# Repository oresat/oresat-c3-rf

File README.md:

# oresat-c3-rf
RF Sub systems for the C3 board.  This includes the transeiver ICs and all front-end components for the uplink and downlink radios.

## [AxSem_Profiles](AxSem_Profiles)
These are a bunch of profiles that initialize the AxSem RadioLab configuration program for testing and experiments.

## [KiCad](KiCad)
Evaluation board schematics and layouts in KiCad. Some of the older Eagle CAD boards are here converted to KiCAD.

## [block-diagrams](block-diagrams)
Block diagrams of the L band receiver and UHF transceiver hardware.

## [bom](bom)
Inventory and bill-of-materials (BOMs) for evaluation boards.

## [eagle](eagle)
Evaluation board schematics and layouts in EAGLE CAD.

## [link-models](link-models)
Complete link models for command/engineering channels, telemetry/public channels, and bulk mission data channels.

## [measurements](measurements)
Evaluation board measurements using lab tools.

## [simulations](simulations)
Evaluation board simulations using ADS and/or HFSS.

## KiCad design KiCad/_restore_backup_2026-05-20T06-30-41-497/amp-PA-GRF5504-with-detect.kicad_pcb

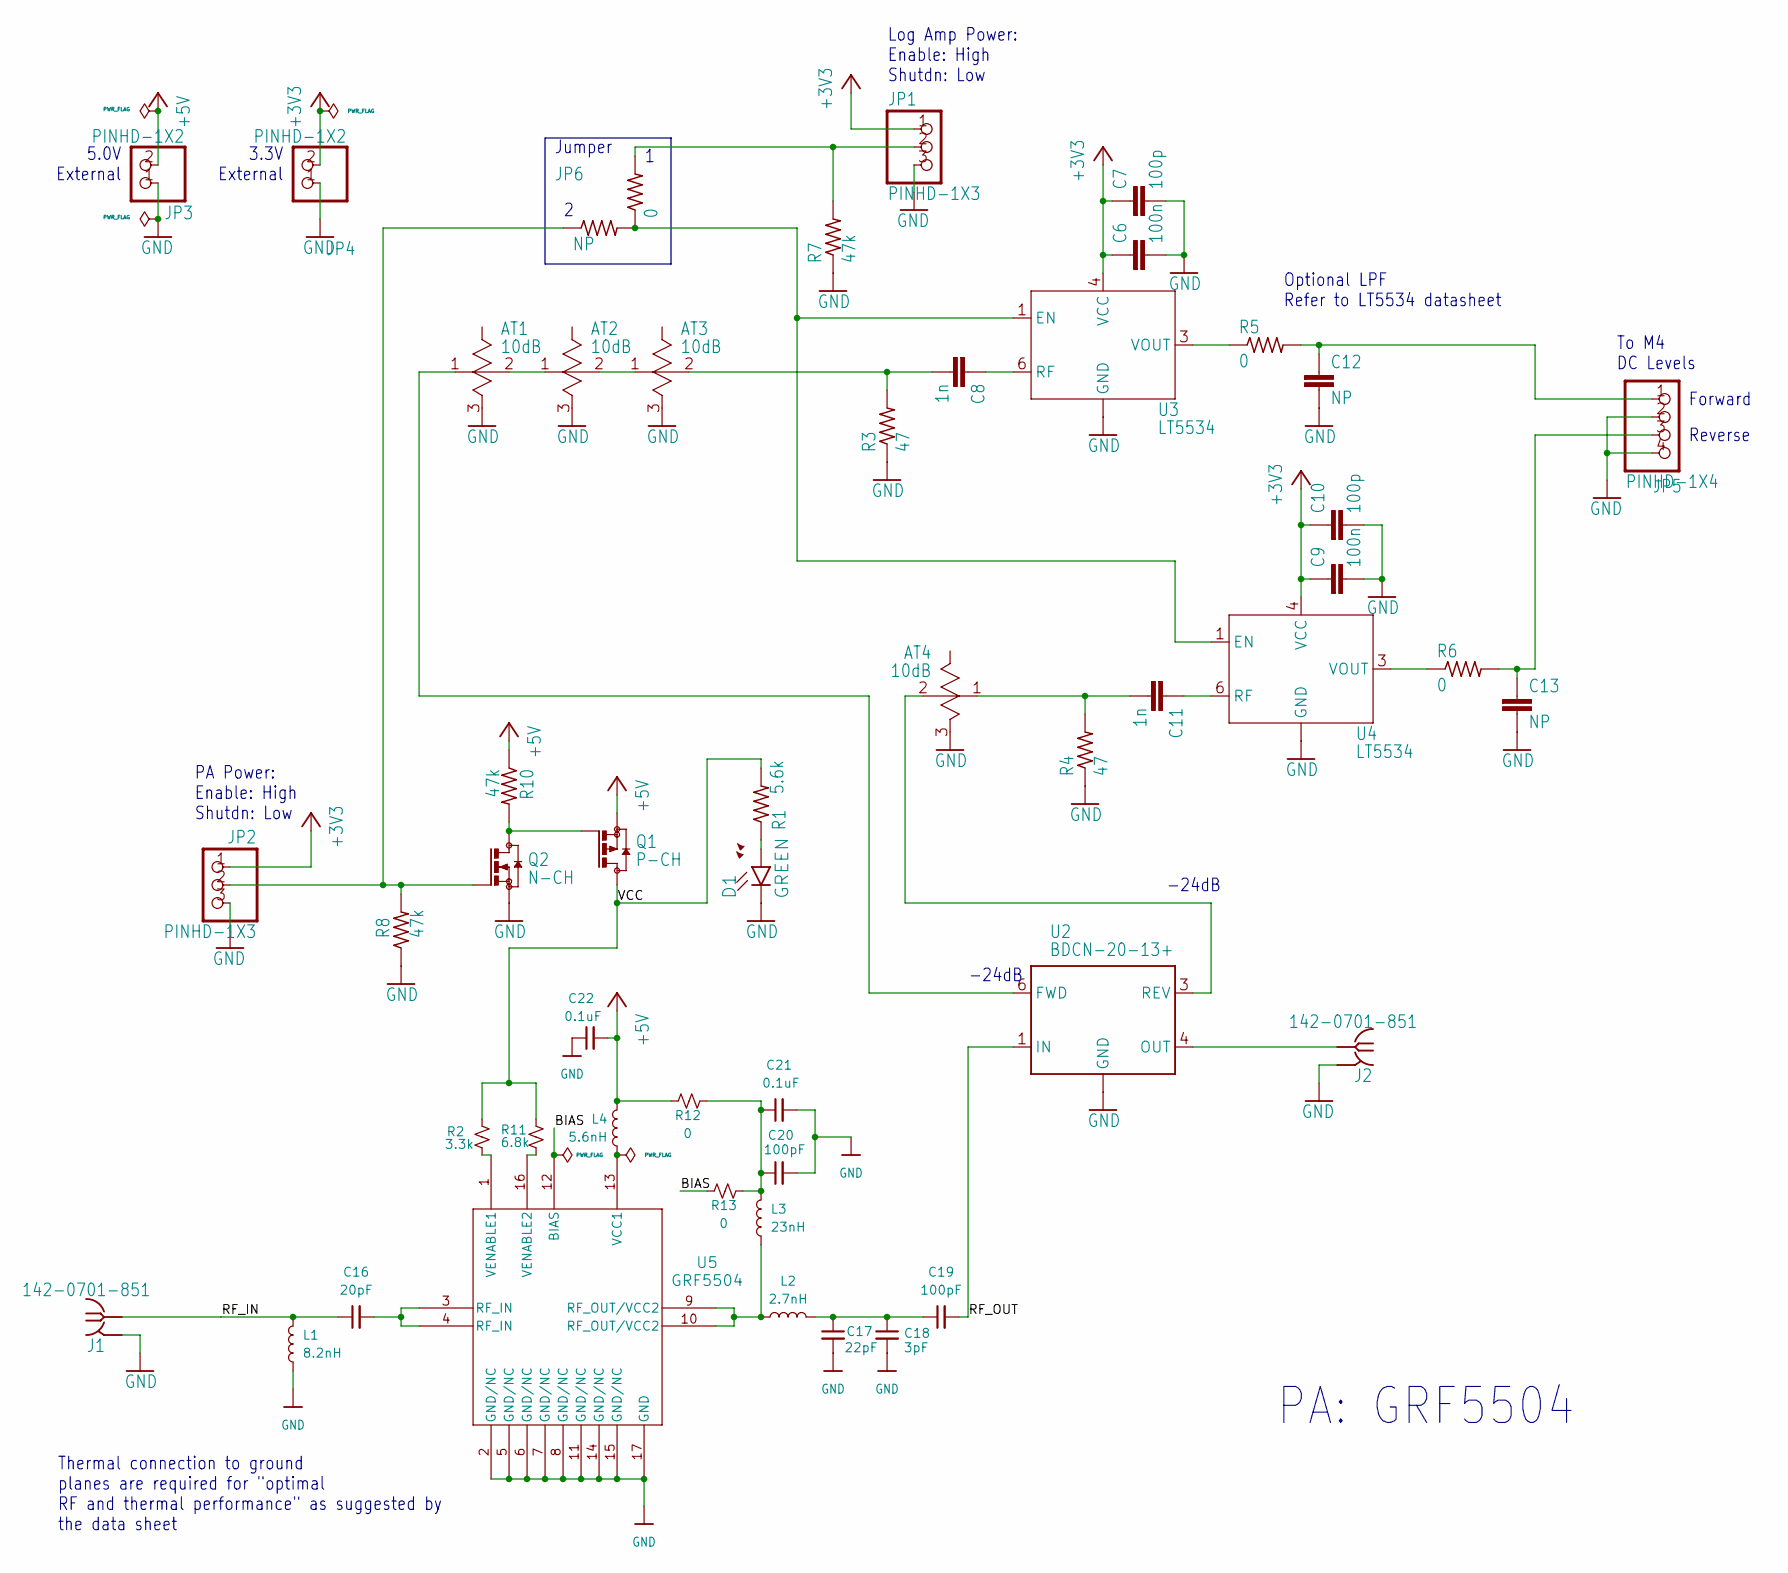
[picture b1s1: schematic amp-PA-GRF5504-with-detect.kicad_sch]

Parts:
AT1: 10dB; 0805
AT2, AT3, AT4: 10dB; 0603
C6, C9: 100n; .0603-B-NOSILK
C7, C10: 100p; .0603-B-NOSILK
C8, C11: 1n; .0402-C-NOSILK
C12, C13: NP; .0603-B-NOSILK
C16: 20pF; .0402-B-NOSILK-GRJ15-GRM15-MURATA-CAPS
C17: 22pF; .0402-B-NOSILK-GRJ15-GRM15-MURATA-CAPS
C18: 3pF; .0402-B-NOSILK-GRJ15-GRM15-MURATA-CAPS
C19, C20: 100pF; .0402-B-NOSILK-GRJ15-GRM15-MURATA-CAPS
C21, C22: 0.1uF; .0402-B-NOSILK-GRJ15-GRM15-MURATA-CAPS
D1: GREEN; LED-0603
J1, J2: 142-0701-851
JP1, JP2: PINHD-1X3; 1X03_325
JP3, JP4: PINHD-1X2; 1X02_325
JP5: PINHD-1X4; 1X04_325
JP6: NP; .0603-B-NOSILK
L1: 8.2nH; .0402-B-NOSILK-LQG-MURATA-INDUCTOR
L2: 2.7nH; .0603-B-NOSILK-DC-COILCRAFT-INDUCTOR
L3: 23nH; 0908-0908SQ-COILCRAFT-INDUCTOR
L4: 5.6nH; .0402-B-NOSILK-HP-DIGITALELECTRONICS-INDUCTOR
Q1: P-CH; SOT23-6
Q2: N-CH; SOT23-6
R1: 5.6k; .0603-B-NOSILK
R2: 3.3k; .0402-B-NOSILK
R3, R4: 47; .0402-C-NOSILK
R5, R6, R9, R12, R13: 0; .0603-B-NOSILK
R7, R8, R10: 47k; .0402-B-NOSILK
R11: 6.8k; .0402-B-NOSILK
U2: BDCN-20-13+
U3, U4: LT5534; SC70
U5: GRF5504; QFN-16_3MM_GRF

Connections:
+3V3: C6.1, C7.1, C9.1, C10.1, JP1.1, JP2.1, JP4.2, U3.4 (VCC), U4.4 (VCC)
+5V: C22.2, JP3.2, L4.1, Q1.2 (S), R10.1, R12.1
/BIAS: R13.1, U5.12 (BIAS)
/RF_IN: C16.1, J1.RF1 (RF), L1.1
/RF_OUT: C19.2, U2.1 (IN)
/VCC: Q1.3 (D), R1.2, R2.1, R11.1
GND: AT1.3 (GND), AT2.3 (GND), AT3.3 (GND), AT4.3 (GND), C6.2, C7.2, C9.2, C10.2, C12.2, C13.2, C17.2, C18.2, C20.2, C21.2, C22.1, D1.C, J1.GND1 (GND), J1.GND2 (GND), J1.GND3 (GND), J1.GND4 (GND), J2.GND1 (GND), J2.GND2 (GND), J2.GND3 (GND), J2.GND4 (GND), JP1.3, JP2.3, JP3.1, JP4.1, JP5.2, JP5.4, L1.2, Q2.2 (S), R3.1, R4.1, R7.1, R8.1, U2.2 (GND), U2.5 (GND), U3.2 (GND), U3.5 (GND), U4.2 (GND), U4.5 (GND), U5.2 (GND/NC), U5.5 (GND/NC), U5.6 (GND/NC), U5.7 (GND/NC), U5.8 (GND/NC), U5.11 (GND/NC), U5.14 (GND/NC), U5.15 (GND/NC), U5.17 (GND)
unnamed: AT1.2, AT2.1
unnamed: AT2.2, AT3.1
unnamed: AT3.2, C8.2, R3.2
unnamed: AT4.1, C11.2, R4.2
unnamed: C12.1, JP5.1, R5.2
unnamed: C13.1, JP5.3, R6.2
unnamed: C16.2, U5.3 (RF_IN), U5.4 (RF_IN)
unnamed: C17.1, C18.1, C19.1, L2.2
unnamed: C20.1, C21.1, L3.2, R12.2, R13.2
unnamed: D1.A, R1.1
unnamed: J2.RF1 (RF), U2.4 (OUT)
unnamed: JP1.2, R7.2, R9.2
unnamed: L2.1, L3.1, U5.9 (RF_OUT/VCC2), U5.10 (RF_OUT/VCC2)
unnamed: Q1.1 (G), Q2.3 (D), R10.2
unnamed: JP2.2, JP6.1, Q2.1 (G), R8.2
unnamed: AT1.1, U2.6 (FWD)
unnamed: AT4.2, U2.3 (REV)
unnamed: JP6.2, R9.1, U3.1 (EN), U4.1 (EN)
unnamed: C8.1, U3.6 (RF)
unnamed: R5.1, U3.3 (VOUT)
unnamed: C11.1, U4.6 (RF)
unnamed: R6.1, U4.3 (VOUT)
unnamed: L4.2, U5.13 (VCC1)
unnamed: R2.2, U5.1 (VENABLE1)
unnamed: R11.2, U5.16 (VENABLE2)

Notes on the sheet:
PA Power: Enable: High Shutdn: Low
Log Amp Power: Enable: High Shutdn: Low
3.3V External
To M4 DC Levels
-24dB
Jumper
PA: GRF5504
Optional LPF Refer to LT5534 datasheet
Thermal connection to ground planes are required for "optimal RF and thermal performance" as suggested by the data sheet
Forward
5.0V External
Reverse

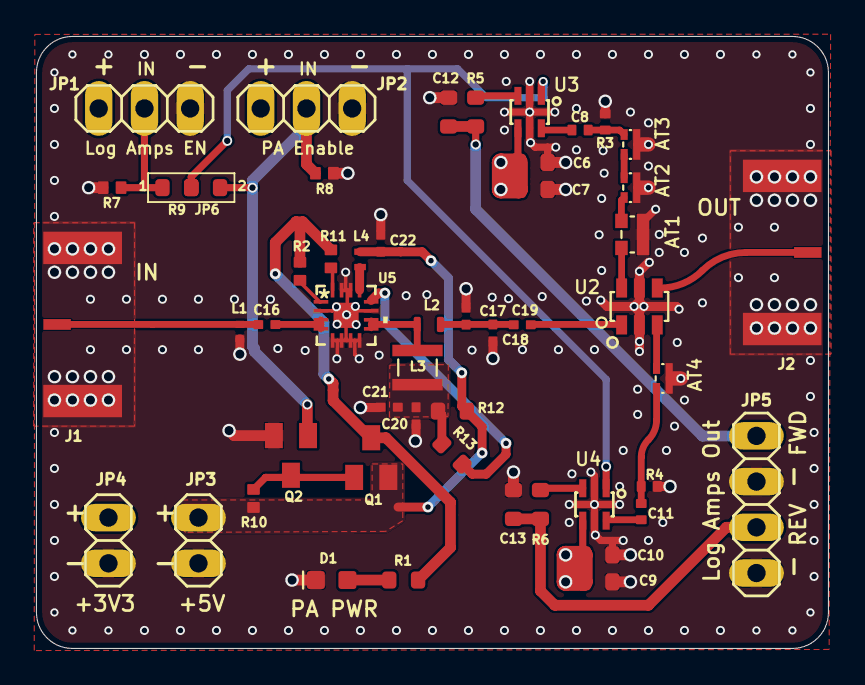
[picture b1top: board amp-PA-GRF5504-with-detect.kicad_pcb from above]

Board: 4 copper layers, 44.0 x 34.0 mm, 51 parts (0 on the bottom side), 32 nets.

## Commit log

2018-10-02 Initial versions
2018-10-02 Block-diagram updates
2018-10-12 Generic card as a starting point.
2018-10-12 move LNA on L band
2018-10-19 Initial link model for primary uplink & downlink
2018-10-19 Fix initial downlink receiver
2019-01-28 Create readme.md
    Start documenting the contents of Vigely's link models.
2019-01-31 Notes
2019-01-31 Added noise temp. calculator for post LNA field on receivers page.
2019-03-27 Updated block diagrams
2019-03-27 Initial schematic
2019-03-27 Add optional BPF on Tx
2019-04-07 Rename
2019-04-07 Delete
2019-04-07 Front-end revisions
2019-04-08 Block diagram updates
2019-04-09 RF Detectors
2019-04-09 Add RL to VSWR
2019-04-12 Add DC levels and fix ANT pinout
2019-04-14 Update to match L band v2.1 block diagram and minor fixes
2019-04-14 Initial secondary uplink (UHF), uplink Tx and antenna need update
2019-04-14 Add BPF after 2nd LNA and add minor details
2019-04-15 Add Friis noise temp calculators
2019-04-15 Update calculator
2019-04-15 Update link-models readme, add Friis calculators
2019-04-16 Update G.S. feed and BPF
2019-04-16 Update G.S. details
2019-04-24 Update G.S. and modulations
2019-04-24 Update power levels
2019-05-05 Diagrams on Tx/Rx sheets, reduce Tx level, notes
2019-05-05 Initial BOM
2019-05-06 Customize and fix summary sheet
2019-05-08 Title notes
2019-05-10 Formatting
2019-05-17 Add UHF G.S. switch. Fix S/C point loss. Adjust Tx power.
2019-05-31 Updated logic
2019-05-31 Eagle descriptions
2019-05-31 Initial Eagle dev boards
2019-05-31 Gnd fix
2019-06-04 Update backplane losses, S/C ant, & PA levels
2019-06-04 Updates from design review
2019-06-21 Add SMPM barrel. Update SC VSWR. Update SNR method.
2019-06-21 Update to reflect link model changes
2019-06-21 Oops, forgot date update.
2019-07-03 Initial OSH Park 4-layer analysis in HFSS
2019-07-08 Added online calculator comparison
2019-07-15 Microstrip 4-layer test board
2019-07-15 Rcvd Infineon LNA and IF SAW
2019-07-19 Revise passives, add TCXO options
2019-07-19 Add LDO, LED on auxout
2019-07-24 Add synthesizer-RF-Si4123.brd
2019-07-25 Add 0ohm to TCXO, & minor tweaks.
2019-07-25 Fix fonts
2019-07-25 Change resistor sizes. Add tstop to L1/2 traces.
2019-07-25 Flip batt header
2019-07-30 Added stitching
2019-07-31 Adding parts for synthesizer-RF-Si4123
2019-07-31 Update cap values
2019-08-06 Added lost breakout board for the AX5043 development modules we purchased.
2019-08-07 added silkscreen and some ground plane stitching for funsies
2019-08-08 added manufacturing preview for ax5043 breakouts
2019-08-08 Better TPLACE labels.
2019-08-10 New boms and inventory
2019-08-10 New bom structure
2019-08-10 Update LED resistor
2019-08-13 Add features and minor fixes
2019-08-13 Rename TQP3M9036 to 903x
2019-08-13 Update passives' footprint
2019-08-13 Add TQP3M903x initial layout
2019-08-13 Completed TQP3M903x layout
2019-08-17 Add parts to inventory
2019-08-17 Tune S band
2019-08-17 Minor fixes
2019-08-17 Add optional center bottom coax gnd pad
2019-08-17 Adjust S band matching and add RF component MFG PNs
2019-08-17 Add optional choke, and organize
2019-08-20 "auto-generated from update_repos.py"
2019-08-21 Add separate UHF, L, and S band LNA evals with TQP3M9036/7
2019-08-21 Add top label
2019-08-21 Change SMA via sizes
2019-08-22 Add initial layout
2019-08-22 Add stitching and finalize
2019-08-23 Increase IF bend radius
2019-08-23 Adjust RF clearance
2019-08-23 Add IF-SAW-856930 layout
2019-08-23 Adjust stop mask
2019-08-23 Add direction labels
2019-08-24 Assembled 1x dual-synthesizer board
2019-08-24 Update SMA footprint
2019-08-31 Initial LO amp schematic
2019-08-31 Needs revision
2019-08-31 Fix RF clearance
2019-08-31 Added enable control, and sync options for switching
2019-09-08 Finish layout
2019-09-08 Finish TPS6211x layout
2019-09-08 Add adjust for LP38692
2019-09-08 Notes for TPS6211x
2019-09-09 Add adj and power bad LED for TPS6211x
2019-09-09 Change res sizes for LP38692
2019-09-09 Move old block diagrams
2019-09-09 Updated S/C receiver LNAs with Infineon
2019-09-09 Add public downlink model
2019-09-09 Updated block diagrams, add Infineon LNA, removed timers, notes
2019-09-09 Add boards inventory sheet
2019-09-09 Received Qorvo LNA boards
2019-09-10 Add Si4112 initial layout
2019-09-10 Minor fix TPS6211x
2019-09-10 Update block diagrams power specs, add power budget
2019-09-10 Spelling
2019-09-10 Update link models formatting
2019-09-11 Add beacon link model using handheld
2019-09-11 Update beacon link model, notes
2019-09-12 Si4123 minor fix
2019-09-12 Si4112 layout finish
2019-09-12 Inventory, update boards
2019-09-12 Inventory, add stencils column for boards
2019-09-12 IF SAW, update microstrip
2019-09-12 Mixer, update microstrip
2019-09-12 Si4112, added better shutdown control
2019-09-13 Si4112, fix shutdown control and add bkup power down battery option
2019-09-14 Si4112 fix note
2019-09-14 Power boards add gnd for mounts
2019-09-14 Si4112 add 1u cap
2019-09-15 Created C3 radios power budget
2019-09-15 Block diagrams, update UHF PA, updates notes
2019-09-15 PA TQP7M9206, some updates, desgin will most likely use TQP7M9205
2019-09-15 LO amp TSY-1XXLNB+, minor updates, ready for initial layout
2019-09-15 Synth LO Si4112, notes
2019-09-16 TSY-1XXLNB+ initial layout
2019-09-16 Board inventory, ordered some boards and stencils
2019-09-17 Rename link models
2019-09-17 Rename link models, OreSat1_link_model_v2.5.5a_...
2019-09-19 Rename microstrip test
2019-09-19 Rename 34-40 microstrip and add 36-38
2019-09-19 Add layout for GPS diplexer
2019-09-19 Initial sch/brd for BGB7xxL7ESD LNAs
2019-09-19 Add layout for AVX BP0805
2019-09-21 BP0805 & diplexer minor fix
2019-09-21 Add layout for BPF-A1340+
2019-09-21 Add layout for BPF-F1250+
2019-09-25 Add/rename BGB741 and finish layout
2019-09-25 L band BPFs minor fixes
2019-09-25 Board inventory update
2019-09-25 L band BP0805 minor fix
2019-09-26 Add BFP740F schematic
2019-09-26 Synth Si4112 change default shutdown
2019-09-26 BOM updates - add IF synth, filters, mixer
2019-09-26 Inventory - add power boms
2019-09-27 Power budget changed mode names
2019-09-29 Changed MiniCirc BPFs to 2-layer and adjusted for CBCPW
2019-09-29 TPS6211x - update values
2019-09-30 Archive boards
2019-09-30 Archive v1 L, S, UHF Qorvo boards. Create wide band TQP3M9037 and optimize for NF
2019-09-30 BGB741 update values
2019-09-30 BFP740F update value
2019-09-30 Inventory - add pwr brd bom variations, add LNA boms, update board inv.
2019-10-02 Mixer - fix tCream for MAC-24+
2019-10-02 BOM - Assembled mixer-MAC-24+
2019-10-02 Update inventory and BOMs for parts received and add TPS62112 bom
2019-10-05 Inventory - assembled boards, updated boms
2019-10-08 synth-si4112 update values
2019-10-08 lna-tqp3m9037 update values
2019-10-08 Inventory and BOMs update
2019-10-13 Inventory update
2019-10-13 Add initial layout for LNA BFP740F
2019-10-13 Update layout for LNA BFP740F
2019-10-14 Finalize layout for LNA BFP740F
2019-10-14 Add initial TRL calibration kit
2019-10-15 Add initial AX5043 schematic
2019-10-16 Finish AX5043 schematic
2019-10-17 Add initial layout AX5043
2019-10-18 Update layout AX5043
2019-10-18 Finalized AX5043 layout
2019-10-19 Update AX5043
2019-10-19 LNA BFP740F fix layout bug
2019-10-19 TRL kit fix layout bug
2019-10-19 AX5043 layout move mark
2019-10-20 Add microstrips measurements on E5071C ENA
2019-10-20 Rename readme
2019-10-20 Add simulations directory
2019-10-20 Add ustrips tests 2019-08-30
2019-10-20 Update READMEs
2019-10-20 Change ustrip width
2019-10-20 Add resized backplane image for TDR
2019-10-21 TRL kit add sStop on ustrips
2019-10-21 Add TDR compare from 2019-08-30
2019-10-21 Add for move
2019-10-26 Update inventory
2019-11-05 Add new quad-hybrid
2019-11-05 Update mixer, minor fix
2019-11-06 Rename QCN-19+
2019-11-06 Update QCN-19+ names
2019-11-06 Update QCN-19+, add optional isolation port
2019-11-08 Rename QCN hybrid
2019-11-08 Update QCN hybrid name
2019-11-11 Update LNA-BFP740F values
2019-11-11 Update AX5043 values
2019-11-11 Add AX5043 and BFP740F LNA BOMs
2019-11-15 Update TRL-cal notes
2019-11-15 Rename calibration-thru-reflect-match-sma
2019-11-15 Update BGB741 MMIC footprint tCream
2019-11-15 Update inventory and BOMs
2019-11-19 Fix tCream on BFP740F
2019-11-19 Update TRM kit, add more stop mask around match
2019-11-22 Add annotated photos
2019-11-29 Add generic 3rd order BPF design
2019-11-29 Add generic 5th order LPF design
2019-11-29 Update 740F LNA, minor polygon fix
2019-12-01 Add L band hairpin filter
2019-12-02 Update L band hairpin
2019-12-07 Update values
2019-12-16 Update link models
2019-12-29 Archive BFP740F v1
2019-12-29 Add Infineon BFPxxxF LNA v2
2020-01-14 Archive v3 block diagrams
2020-01-14 Update block diagrams
2020-02-06 Archive L band v4.0 block diagram
2020-02-06 Update L band block diagram
2020-03-03 Update current BFPxxxF
2020-03-03 Update BGB741L7ESD
2020-03-05 Add tuned mixer schematic
2020-03-22 Add v2 switch
2020-07-22 Phase velocity correction
2020-07-29 Add TQP7M9105 PA schematic and initial layout.
2020-07-31 Update PA TQP7M9105 schematic
2020-07-31 Update PA layout placement
2020-08-01 Update PA TQP7M9105 layout
2020-08-01 Update UHF PA board
2020-08-20 Update PA TQP7M9105 values
2020-08-20 Add UHF PA dev board BOM
2022-02-07 Provide Radiolab profiles in subdirectory AxSem_Profiles
2022-02-08 Create README.md
    Adding description of RadioLab profiles
2022-02-08 Update README.md
    Finish description of files
2022-02-09 Update README.md
    Put details into a table
2026-02-23 Swapped TQP7M9105 chip for GRF5504
2026-02-23 added to gitignore file
2026-02-23 added to gitignore
2026-02-23 added stuff to gitignore
2026-02-23 cleared some of the DRC errors
2026-02-23 cleared all ERC warnings
2026-02-24 Update README.md
    KiCAD folder description.
2026-02-25 Excluded remaining DRC errors
2026-02-25 updated BOM
2026-02-27 updated comments on schematic
2026-05-20 Cleaned up libraries and paths
2026-05-20 removed .history folder
2026-05-20 mess
